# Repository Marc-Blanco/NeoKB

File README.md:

# NeoKB
-----------------
## The ultimate split keyboard 

It has different modes and writable functions, It has a mouse incorporated to never move your fingers away from the keys and a potenciometer to control the volume or whatever you would like it to do. A versatile multifunctional comfortable keyboard.

### BOM: 
| Item | Qty | Supplier | Cost/item | Total Cost | link |
| --- | --- | --- | --- | --- | --- |
| Raspberry Pi Pico | 2 | KUBII | $5.37 | $10.74 | https://www.kubii.com/es/microcontroladores/3205-1639-raspberry-pi-pico-w-h-wh-3272496311589.html#/version_pico-pico |
| Trackball sensor | 1 | MusRock | $9.97 | $9.97 | https://www.amazon.com/Trackball-360-Degree-Rotation-BlackBerry-Breakout/dp/B0GKFGNC8S?crid=1CO8YQCV54AKE&dib=eyJ2IjoiMSJ9.18rAVinrqTohvHfsupcKaHjYAskeK8hsWJgHdPv9yO2y4OlZiC1-EIhue1jALwilmcLU7EHLJ-Zu5RVopirPmQGzHz6XBdemFKgaiXzNI3Y.iC7uxYI_3l1AeEnnQa2uwib01CTnnOSsnRklyWU781Y&dib_tag=se&keywords=trackball+breakout&qid=1791468810&sprefix=trackball+break%2Caps%2C343&sr=8-1 |
| Switches | 50 | Aliexpress? | $0.10 | $5.00 | https://www.aliexpress.com/ssr/300000512/BundleDealsDutyCovered?spm=a2g0o.productlist.main.8.5d4c55e9M10oyi&businessCode=guide&productIds=1005012943053796%3A12000059828315871&pha_manifest=ssr&_immersiveMode=true&disableNav=YES&sourceName=SEARCHProduct&utparam-url=scene%3Asearch%7Cquery_from%3A%7Cx_object_id%3A1005012943053796%7C_p_origin_prod%3A&pvid=1eb1c5b9-ddc8-4fef-b824-7e70e77da587 |
| PCB | 1 | JLBPCB | $40.00 | $40.00 | https://cart.jlcpcb.com/shopcart/cart/ |
| Estimated total shipping | 1 |  |  | $26.59 |  |

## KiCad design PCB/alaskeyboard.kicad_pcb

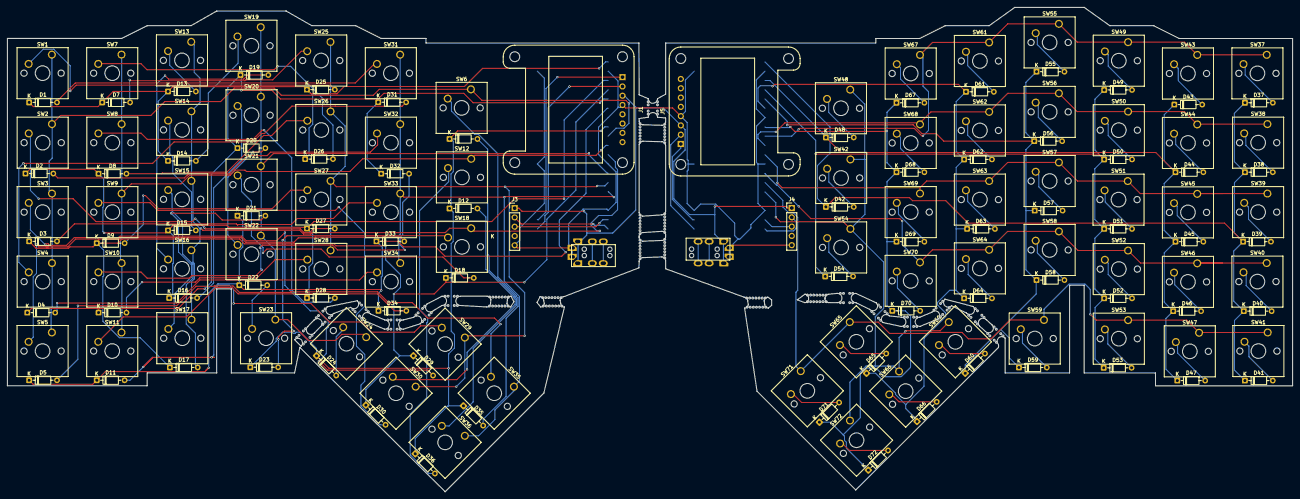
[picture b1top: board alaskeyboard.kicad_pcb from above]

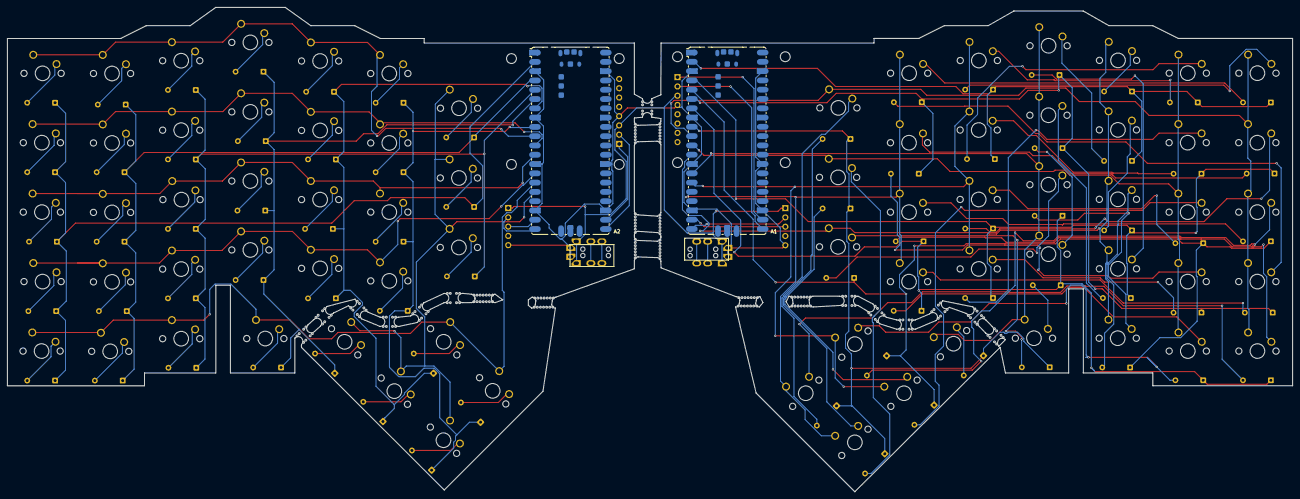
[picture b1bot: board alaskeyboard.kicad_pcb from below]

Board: 2 copper layers, 351.6 x 132.5 mm, 179 parts (2 on the bottom side), 106 nets.

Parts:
A1, A2: RaspberryPi_Pico; RaspberryPi_Pico_SMD
B1, B1#2, B1#3, B1#4, B1#5, B2, B17, B17#2, B17#3, B17#4, B17#5, B17#6, B18: MouseBite; MouseBite-Slot_2.54x2.54mm_on-edge_D0.5mm_P0.85mm_4h_Trace
B3, B5, B6, B8, B9, B10, B11, B11#2, B11#3, B11#4, B12, B14, B19, B20: MouseBite; MouseBite-Part_2.0x4.5mm_outset_D0.5mm_P0.85mm_7h
D1, D2, D3, D4, D5, D6, D7, D8, D9, D10, D11, D12, D13, D14, D15, D16, D17, D18, D19, D20, D21, D22, D23, D24, D25, D26, D27, D28, D29, D30, D31, D32, D33, D34, D35, D36, D37, D38, D39, D40, D41, D42, D43, D44, D45, D46, D47, D48, D49, D50, D51, D52, D53, D54, D55, D56, D57, D58, D59, D60, D61, D62, D63, D64, D65, D66, D67, D68, D69, D70, D71, D72: 1N914; D_DO-35_SOD27_P7.62mm_Horizontal
J1, J5: Conn_01x04; Adafruit_SSD1306
J2, J6: MJ-4PP-9
J3, J4: Conn_01x05; PinHeader_1x05_P2.54mm_Vertical
SW1, SW2, SW3, SW4, SW5, SW6, SW7, SW8, SW9, SW10, SW11, SW12, SW13, SW14, SW15, SW16, SW17, SW18, SW19, SW20, SW21, SW22, SW23, SW24, SW25, SW26, SW27, SW28, SW29, SW30, SW31, SW32, SW33, SW34, SW35, SW37, SW38, SW39, SW40, SW41, SW42, SW43, SW44, SW45, SW46, SW47, SW48, SW49, SW50, SW51, SW52, SW53, SW54, SW55, SW56, SW57, SW58, SW59, SW60, SW61, SW62, SW63, SW64, SW65, SW66, SW67, SW68, SW69, SW70, SW71: SW_Push_45deg; SW_Cherry_MX_1.00u_PCB
SW36, SW72: SW_Cherry_MX_1.00u_PCB

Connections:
/Untitled/Col1: A2.2 (GPIO1), D37.1 (K), D38.1 (K), D39.1 (K), D40.1 (K), D41.1 (K), D42.1 (K)
/Untitled/Col2: A2.4 (GPIO2), D43.1 (K), D44.1 (K), D45.1 (K), D46.1 (K), D47.1 (K), D48.1 (K)
/Untitled/Col3: A2.5 (GPIO3), D49.1 (K), D50.1 (K), D51.1 (K), D52.1 (K), D53.1 (K), D54.1 (K)
/Untitled/Col4: A2.6 (GPIO4), D55.1 (K), D56.1 (K), D57.1 (K), D58.1 (K), D59.1 (K), D60.1 (K)
/Untitled/Col5: A2.7 (GPIO5), D61.1 (K), D62.1 (K), D63.1 (K), D64.1 (K), D65.1 (K), D66.1 (K)
/Untitled/Col6: A2.9 (GPIO6), D67.1 (K), D68.1 (K), D69.1 (K), D70.1 (K), D71.1 (K), D72.1 (K)
/Untitled/Row1: A2.10 (GPIO7), SW37.1, SW43.1, SW49.1, SW55.1, SW61.1, SW67.1
/Untitled/Row2: A2.11 (GPIO8), SW38.1, SW44.1, SW50.1, SW56.1, SW62.1, SW68.1
/Untitled/Row3: A2.12 (GPIO9), SW39.1, SW45.1, SW51.1, SW57.1, SW63.1, SW69.1
/Untitled/Row4: A2.14 (GPIO10), SW40.1, SW46.1, SW52.1, SW58.1, SW64.1, SW70.1
/Untitled/Row5: A2.15 (GPIO11), SW41.1, SW47.1, SW53.1, SW59.1, SW65.1, SW71.1
/Untitled/Row6: A2.16 (GPIO12), SW42.1, SW48.1, SW54.1, SW60.1, SW66.1, SW72.1
/Untitled/SCL: A2.21 (GPIO16), J5.2
/Untitled/SCL2: A2.19 (GPIO14), J4.3
/Untitled/SDA: A2.22 (GPIO17), J5.1
/Untitled/SDA2: A2.20 (GPIO15), J4.2
/alaskeyboard/Col1: A1.2 (GPIO1), D1.1 (K), D7.1 (K), D13.1 (K), D14.1 (K), D25.1 (K), D26.1 (K)
/alaskeyboard/Col2: A1.4 (GPIO2), D2.1 (K), D8.1 (K), D15.1 (K), D16.1 (K), D27.1 (K), D28.1 (K)
/alaskeyboard/Col3: A1.5 (GPIO3), D3.1 (K), D9.1 (K), D17.1 (K), D18.1 (K), D29.1 (K), D30.1 (K)
/alaskeyboard/Col4: A1.6 (GPIO4), D4.1 (K), D10.1 (K), D19.1 (K), D20.1 (K), D31.1 (K), D32.1 (K)
/alaskeyboard/Col5: A1.7 (GPIO5), D5.1 (K), D11.1 (K), D21.1 (K), D22.1 (K), D33.1 (K), D34.1 (K)
/alaskeyboard/Col6: A1.9 (GPIO6), D6.1 (K), D12.1 (K), D23.1 (K), D24.1 (K), D35.1 (K), D36.1 (K)
/alaskeyboard/Row1: A1.10 (GPIO7), SW1.1, SW2.1, SW3.1, SW4.1, SW5.1, SW6.1
/alaskeyboard/Row2: A1.11 (GPIO8), SW7.1, SW8.1, SW9.1, SW10.1, SW11.1, SW12.1
/alaskeyboard/Row3: A1.12 (GPIO9), SW13.1, SW14.1, SW15.1, SW16.1, SW17.1, SW18.1
/alaskeyboard/Row4: A1.14 (GPIO10), SW19.1, SW20.1, SW21.1, SW22.1, SW23.1, SW24.1
/alaskeyboard/Row5: A1.15 (GPIO11), SW25.1, SW26.1, SW27.1, SW28.1, SW29.1, SW30.1
/alaskeyboard/Row6: A1.16 (GPIO12), SW31.1, SW32.1, SW33.1, SW34.1, SW35.1, SW36.1
/alaskeyboard/SCL: A1.21 (GPIO16), J1.2
/alaskeyboard/SCL2: A1.19 (GPIO14), J3.3
/alaskeyboard/SDA: A1.22 (GPIO17), J1.1
/alaskeyboard/SDA2: A1.20 (GPIO15), J3.2
GND: A1.3 (GND), A1.8 (GND), A1.13 (GND), A1.18 (GND), A1.23 (GND), A1.28 (GND), A1.38 (GND), A2.3 (GND), A2.8 (GND), A2.13 (GND), A2.18 (GND), A2.23 (GND), A2.28 (GND), A2.38 (GND), J1.4, J2.1, J3.5, J4.5, J5.4, J6.1
unnamed: D1.2 (A), SW31.2
unnamed: D2.2 (A), SW32.2
unnamed: D3.2 (A), SW33.2
unnamed: D4.2 (A), SW34.2
unnamed: D5.2 (A), SW35.2
unnamed: D6.2 (A), SW36.2
unnamed: D7.2 (A), SW25.2
unnamed: D8.2 (A), SW26.2
unnamed: D9.2 (A), SW27.2
unnamed: D10.2 (A), SW28.2
unnamed: D11.2 (A), SW29.2
unnamed: D12.2 (A), SW30.2
unnamed: D13.2 (A), SW13.2
unnamed: D14.2 (A), SW19.2
unnamed: D15.2 (A), SW14.2
unnamed: D16.2 (A), SW20.2
unnamed: D17.2 (A), SW15.2
unnamed: D18.2 (A), SW21.2
unnamed: D19.2 (A), SW16.2
unnamed: D20.2 (A), SW22.2
unnamed: D21.2 (A), SW17.2
unnamed: D22.2 (A), SW23.2
unnamed: D23.2 (A), SW18.2
unnamed: D24.2 (A), SW24.2
unnamed: D25.2 (A), SW1.2
unnamed: D26.2 (A), SW7.2
unnamed: D27.2 (A), SW2.2
unnamed: D28.2 (A), SW8.2
unnamed: D29.2 (A), SW3.2
unnamed: D30.2 (A), SW9.2
unnamed: D31.2 (A), SW4.2
unnamed: D32.2 (A), SW10.2
unnamed: D33.2 (A), SW5.2
unnamed: D34.2 (A), SW11.2
unnamed: D35.2 (A), SW6.2
unnamed: D36.2 (A), SW12.2
unnamed: D37.2 (A), SW37.2
unnamed: D38.2 (A), SW38.2
unnamed: D39.2 (A), SW39.2
unnamed: D40.2 (A), SW40.2
unnamed: D41.2 (A), SW41.2
unnamed: D42.2 (A), SW42.2
unnamed: D43.2 (A), SW43.2
unnamed: D44.2 (A), SW44.2
unnamed: D45.2 (A), SW45.2
unnamed: D46.2 (A), SW46.2
unnamed: D47.2 (A), SW47.2
unnamed: D48.2 (A), SW48.2
unnamed: D49.2 (A), SW49.2
unnamed: D50.2 (A), SW50.2
unnamed: D51.2 (A), SW51.2
unnamed: D52.2 (A), SW52.2
unnamed: D53.2 (A), SW53.2
unnamed: D54.2 (A), SW54.2
unnamed: D55.2 (A), SW55.2
unnamed: D56.2 (A), SW56.2
unnamed: D57.2 (A), SW57.2
unnamed: D58.2 (A), SW58.2
unnamed: D59.2 (A), SW59.2
unnamed: D60.2 (A), SW60.2
unnamed: D61.2 (A), SW61.2
unnamed: D62.2 (A), SW62.2
unnamed: D63.2 (A), SW63.2
unnamed: D64.2 (A), SW64.2
unnamed: D65.2 (A), SW65.2
unnamed: D66.2 (A), SW66.2
unnamed: D67.2 (A), SW67.2
unnamed: D68.2 (A), SW68.2
unnamed: D69.2 (A), SW69.2
unnamed: D70.2 (A), SW70.2
unnamed: D71.2 (A), SW71.2
unnamed: D72.2 (A), SW72.2
VCC: J1.3, J2.2, J3.1, J4.1, J5.3, J6.2
